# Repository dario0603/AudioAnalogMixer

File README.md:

# Analog Audio Mixer

## Overview

Design and development of a **modular analog audio mixer**, combining circuit simulation and PCB design. The project focuses on audio signal conditioning, equalization, level control, and the integration of multiple input channels into a modular mixer architecture.

The design is divided into two main development areas:

- **LTspice simulations:** individual analog circuit blocks are simulated and evaluated before hardware implementation.
- **KiCad designs:** modular PCB boards are developed to organize the mixer circuitry into functional sections.

The current design includes microphone/line signal conditioning, a three-band equalizer, level and FX-send circuitry, a clipping indicator, and a four-channel mixer board.

The project is still under development. Circuit design, simulation, and PCB integration are ongoing, and the current files should be considered work in progress rather than a finalized hardware design.

## System Architecture

The mixer is organized into modular functional blocks. This approach makes it possible to develop and test each section independently before integrating the complete system.
The input stage provides microphone and line-level signal conditioning. Separate configurations are included for a single microphone/line channel and for two line-level channels, intended for left and right stereo signals.

The signal-conditioning section includes:

- Microphone/line preamplification.
- Three-band tone control.
- Output-level adjustment.
- FX-send circuitry.

### 1. Microphone/Line Preamplifier Circuit

The microphone/line preamplifier circuit provides input signal conditioning and amplification for low-level microphone signals and line-level audio sources. It is designed to adapt different input signal levels to the following stages of the mixer, ensuring proper signal amplification and compatibility with the audio processing circuitry.

### 2. Three-Band Equalizer

The three-band equalizer provides independent control over the low-, mid-, and high-frequency portions of the audio spectrum.

The frequency response is evaluated through LTspice AC analysis. Different equalizer settings are compared to investigate how the circuit affects the audio signal across the frequency range.

### 3. Mixer Unit

This stage combines the signals processed by the input stages (microphone/line preamplifier and three-band equalizer), summing the individual channels to generate the final audio output. The output is provided in differential mode through two dedicated buffer amplifiers, ensuring proper signal driving capability and output impedance.

### 4. Clipping Indicator

A dedicated clipping-indicator circuit is included in the LTspice project.

The circuit uses an LM393 comparator model to detect signal levels approaching the selected clipping threshold. The output can be used to drive an LED, providing a visual indication of excessive signal amplitude.

The comparator circuit is simulated separately to allow its operation and threshold behavior to be evaluated independently of the complete mixer.

## Simulations

### 1. Three-Band Equalizer

**Frequency Response Analysis**

The frequency response of the three-band equalizer is analyzed for different control settings, including low-frequency, mid-frequency, and high-frequency attenuation.

| Low-frequency cut | Mid-frequency cut | High-frequency cut |
|:---:|:---:|:---:|
|  |  |  |

**Flat Frequency Response Analysis**

The overall frequency response is evaluated with all equalizer controls set to their neutral positions.

**Monte Carlo Frequency Response Analysis**

A Monte Carlo analysis is performed to evaluate the effect of component tolerances on the equalizer response, considering 1% resistor tolerances (0603 package) and 10% ceramic X7R capacitor tolerances.

### 2. Microphone/Line Preamplifier

**AC Frequency Response Analysis**

The frequency response of the line and XLR preamplifier configurations is evaluated through LTspice AC analysis to characterize their behavior across the audio frequency range.

**Line Preamplifier:**

**XLR Preamplifier:**

**Transient Response Analysis – 5 kHz Differential Input**

A 5 kHz differential sinusoidal signal is applied to the XLR preamplifier to evaluate its transient response under maximum and minimum gain configurations.

**Input Signal:**

**Maximum Gain Configuration:**

**Minimum Gain Configuration:**

**Monte Carlo Transient Analysis**

A Monte Carlo simulation consisting of 300 runs is performed to evaluate the variability of the XLR preamplifier transient response due to component tolerances, considering both maximum and minimum gain configurations.

**Maximum Gain Configuration:**

**Minimum Gain Configuration:**

**Noise Analysis**

LTspice noise analysis is performed to evaluate the output noise spectral density of the preamplifier stages. Different operational-amplifier configurations are compared to investigate their noise contributions.

The noise simulations are still being refined, particularly regarding the accuracy of the operational-amplifier noise models and their consistency with datasheet specifications.

### 3. Mixer

**Transient Response Analysis**

Transient simulations are performed to evaluate the time-domain behavior of the mixer circuit.

**Monte Carlo Transient Analysis**

A Monte Carlo simulation consisting of 300 runs is performed to investigate output voltage variations caused by component tolerances.

.png)

## PCB Design

The PCB development is carried out in KiCad. The modular approach separates the main mixer board from the input signal-conditioning circuitry.

### 1. Four-Channel Mixer Board

The `4ChannelMixerBoard` project contains the PCB design and schematic for the four-channel mixer board.

The board is intended to provide the central platform for combining the individual audio channels.

### 2. Single-Channel Microphone/Line Board

The `SignalConditioning - OneChannel - Mic-Line` project contains the signal-conditioning design for a single microphone/line input channel.
The PCB layout brings the microphone/line preamplifier, three-band equalizer, level and FX-send circuitry, and power supply together on a single board.

The project includes the following schematic sections:

- Microphone/line preamplifier.
- Three-band equalizer.
- Level control and FX-send circuitry.
- Power supply.

### 3. Two-Channel Line Board

The `SignalConditioning - TwoChannels - R-L-Line` project contains a two-channel signal-conditioning configuration intended for right and left line-level signals.

Its schematic is organized around the same functional blocks as the single-channel version, adapted for a stereo input configuration.

The PCB layouts and circuit integration are still under development. Further work is required to complete the board designs and verify their operation in hardware.

## Repository Structure

```text
.
├── README.md
│
├── AudioMixer - LTSpice/
│   ├── 3bEq/
│   │   ├── AudioMixer - 3bEq.asc
│   │   ├── NE5532.sub
│   │   └── Montecarlo/
│   │
│   ├── ClippingLed/
│   │   ├── ClippingLed.asc
│   │   └── lm393.lib
│   │
│   └── Mic-Line amplifier/
│       ├── AudioMixer - Mic-Line-amp.asc
│       └── NE5532.sub
│
├── AudioMixer - ModularBoards/
│   ├── spec.txt
│   │
│   ├── 4ChannelMixerBoard/
│   │   ├── Mixer_circuit.kicad_pro
│   │   ├── Mixer_circuit.kicad_sch
│   │   └── Mixer_circuit.kicad_pcb
│   │
│   ├── SignalConditioning - OneChannel - Mic-Line/
│   │   ├── AudioMixer.kicad_pro
│   │   ├── AudioMixer.kicad_sch
│   │   ├── AudioMixer.kicad_pcb
│   │   ├── Mic-Line_preamp.kicad_sch
│   │   ├── 3_band_equalizer.kicad_sch
│   │   ├── Level_and_FXSend.kicad_sch
│   │   └── Power_supply.kicad_sch
│   │
│   └── SignalConditioning - TwoChannels - R-L-Line/
│       ├── AudioMixer.kicad_pro
│       ├── AudioMixer.kicad_sch
│       ├── AudioMixer.kicad_pcb
│       ├── Mic-Line_preamp.kicad_sch
│       ├── 3_band_equalizer.kicad_sch
│       ├── Level_and_FXSend.kicad_sch
│       └── Power_supply.kicad_sch
│
└── img/
```

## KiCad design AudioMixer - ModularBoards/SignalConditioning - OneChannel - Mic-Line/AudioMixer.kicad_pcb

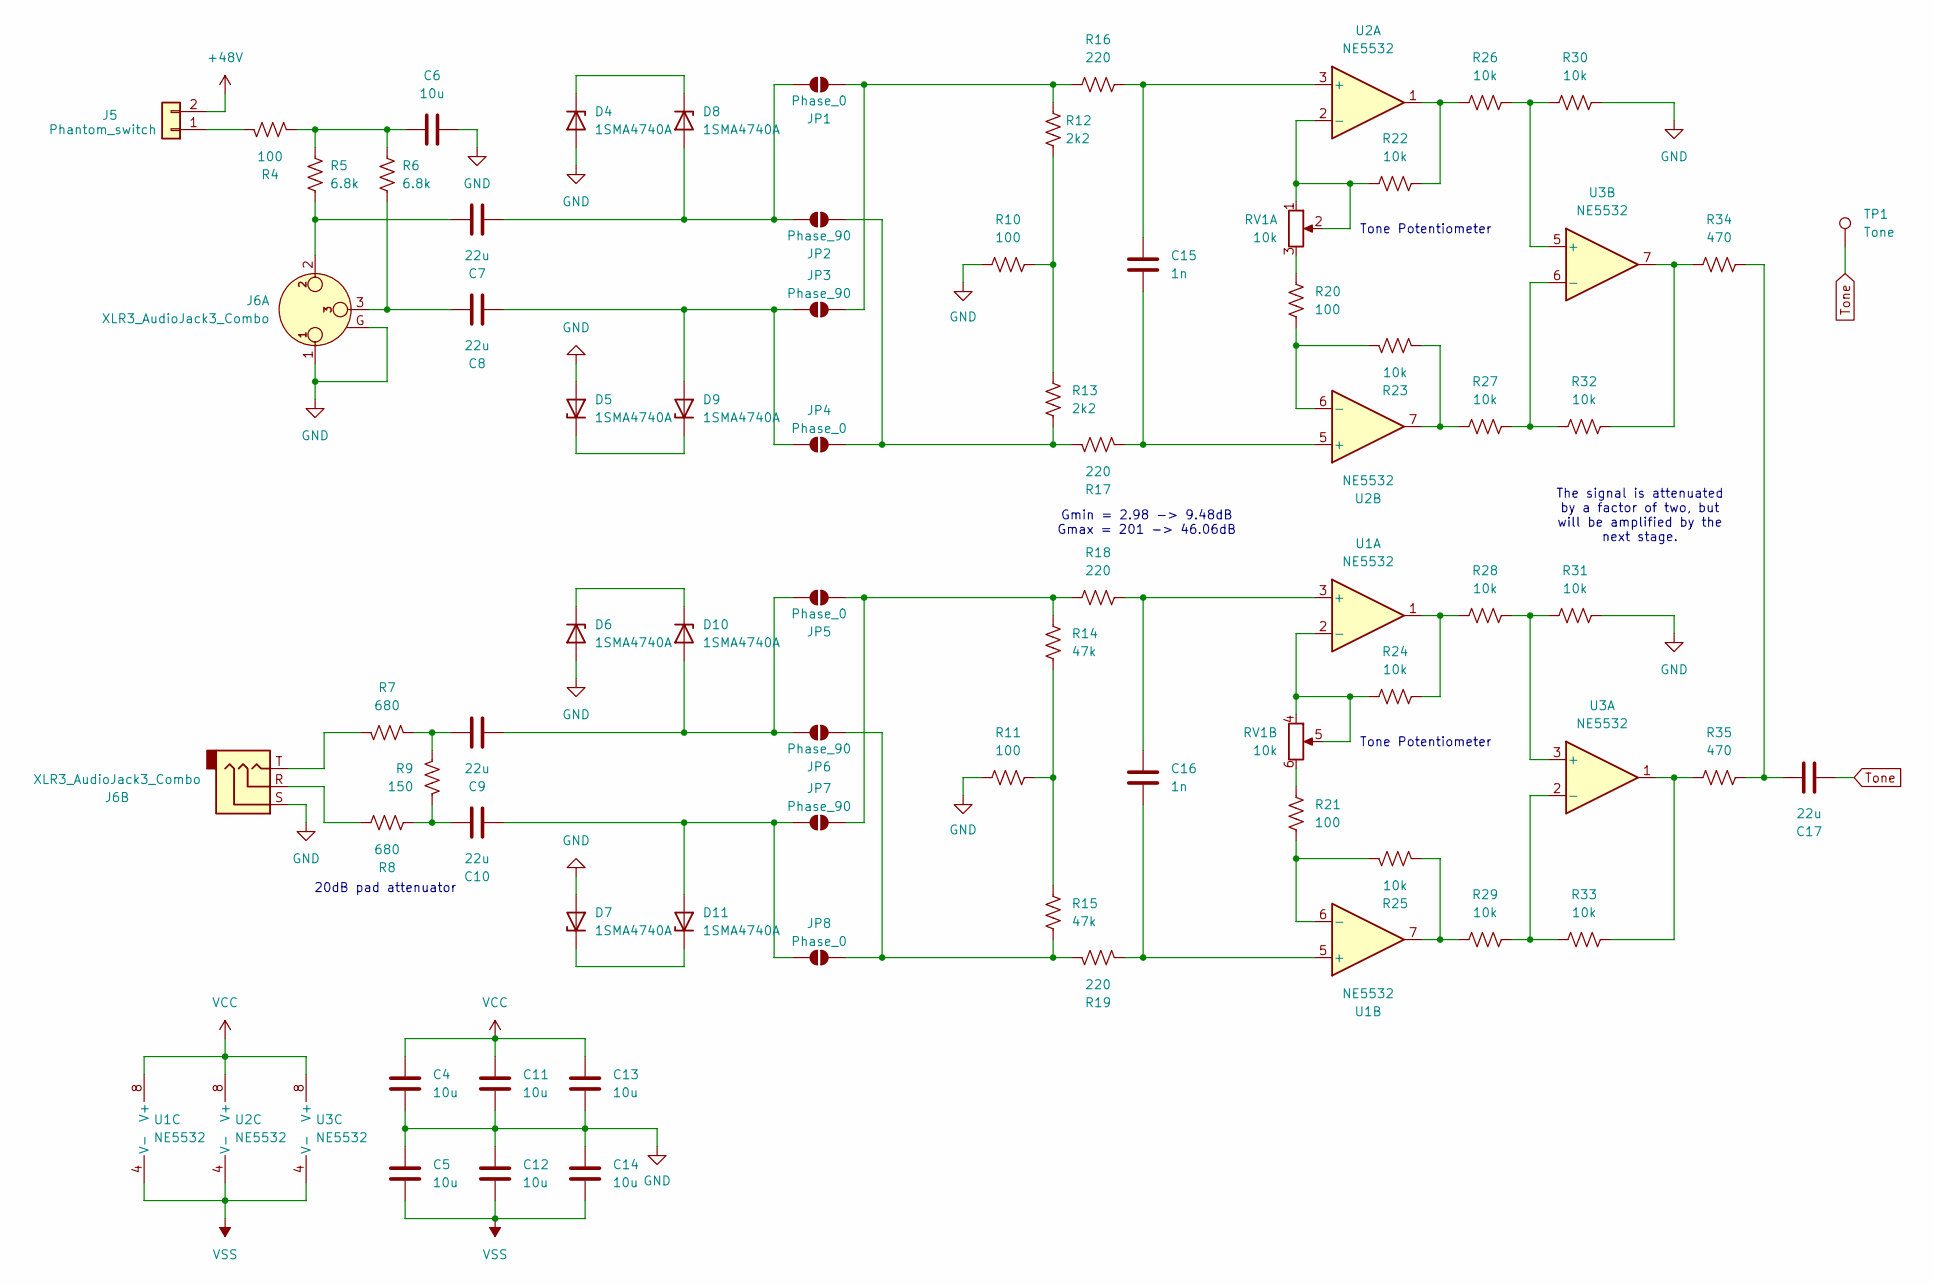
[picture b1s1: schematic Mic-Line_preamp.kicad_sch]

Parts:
C4, C5, C6, C11, C12, C13, C14: 10u; C_0805_2012Metric_Pad1.18x1.45mm_HandSolder
C7, C8, C9, C10, C17: 22u; C_0805_2012Metric_Pad1.18x1.45mm_HandSolder
C15, C16: 1n; C_0603_1608Metric_Pad1.08x0.95mm_HandSolder
D4, D5, D6, D7, D8, D9, D10, D11: 1SMA4740A; D_SMA
J5: Phantom_switch; PinHeader_1x02_P2.54mm_Vertical
J6: XLR3_AudioJack3_Combo; Jack_XLR-6.35mm_Neutrik_NCJ6FI-H_Horizontal
JP1, JP4, JP5, JP8: Phase_0; SolderJumper-2_P1.3mm_Open_RoundedPad1.0x1.5mm
JP2, JP3, JP6, JP7: Phase_90; SolderJumper-2_P1.3mm_Open_RoundedPad1.0x1.5mm
R4: 100; R_1206_3216Metric_Pad1.30x1.75mm_HandSolder
R5, R6: 6.8k; R_1206_3216Metric_Pad1.30x1.75mm_HandSolder
R7, R8: 680; R_0603_1608Metric_Pad0.98x0.95mm_HandSolder
R9: 150; R_0603_1608Metric_Pad0.98x0.95mm_HandSolder
R10, R11, R20, R21: 100; R_0603_1608Metric_Pad0.98x0.95mm_HandSolder
R12, R13: 2k2; R_0603_1608Metric_Pad0.98x0.95mm_HandSolder
R14, R15: 47k; R_0603_1608Metric_Pad0.98x0.95mm_HandSolder
R16, R17, R18, R19: 220; R_0603_1608Metric_Pad0.98x0.95mm_HandSolder
R22, R23, R24, R25, R26, R27, R28, R29, R30, R31, R32, R33: 10k; R_0603_1608Metric_Pad0.98x0.95mm_HandSolder
R34, R35: 470; R_0603_1608Metric_Pad0.98x0.95mm_HandSolder
RV1: 10k; Potentiometer_Alps_RK097_Dual_Horizontal
TP1: Tone; TestPoint_Pad_D1.0mm
U1, U2, U3: NE5532; SOIC-8_3.9x4.9mm_P1.27mm

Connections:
+48V: J5.2; also elsewhere on the board
GND: C4.2, C5.1, C6.1, C11.2, C12.1, C13.2, C14.1, D4.2 (A), D5.2 (A), D6.2 (A), D7.2 (A), J6.1, J6.G, J6.S, R10.1, R11.2, R30.1, R31.1; also elsewhere on the board
unnamed: C6.2, R4.1, R5.2, R6.2
unnamed: C7.1, J6.2, R5.1
unnamed: C8.1, J6.3, R6.1
unnamed: C9.1, R7.2, R9.2
unnamed: C10.1, R8.2, R9.1
unnamed: C17.1, R34.2, R35.2
unnamed: D4.1 (K), D8.1 (K)
unnamed: D5.1 (K), D9.1 (K)
unnamed: C7.2, D8.2 (A), JP1.1 (A), JP2.1 (A)
unnamed: C8.2, D9.2 (A), JP3.1 (A), JP4.1 (A)
unnamed: C9.2, D10.2 (A), JP5.1 (A), JP6.1 (A)
unnamed: D6.1 (K), D10.1 (K)
unnamed: C10.2, D11.2 (A), JP7.1 (A), JP8.1 (A)
unnamed: D7.1 (K), D11.1 (K)
unnamed: J5.1, R4.2
unnamed: J6.R, R8.1
unnamed: J6.T, R7.1
unnamed: JP1.2 (B), JP3.2 (B), R12.1, R16.2
unnamed: JP2.2 (B), JP4.2 (B), R13.2, R17.2
unnamed: JP5.2 (B), JP7.2 (B), R14.1, R18.2
unnamed: JP6.2 (B), JP8.2 (B), R15.2, R19.2
unnamed: R10.2, R12.2, R13.1
unnamed: R11.1, R14.2, R15.1
unnamed: R20.1, RV1.3
unnamed: R21.1, RV1.6
unnamed: R22.1, R26.2, U2.1
unnamed: R23.1, R27.2, U2.7
unnamed: R24.1, R28.2, U1.1
unnamed: R25.1, R29.2, U1.7
unnamed: R32.1, R34.1, U3.7
unnamed: R33.1, R35.1, U3.1
unnamed: C16.1, R18.1, U1.3 (+)
unnamed: R24.2, RV1.4, RV1.5, U1.2 (-)
unnamed: C16.2, R19.1, U1.5 (+)
unnamed: R21.2, R25.2, U1.6 (-)
unnamed: C15.1, R16.1, U2.3 (+)
unnamed: R22.2, RV1.1, RV1.2, U2.2 (-)
unnamed: C15.2, R17.1, U2.5 (+)
unnamed: R20.2, R23.2, U2.6 (-)
unnamed: R28.1, R31.2, U3.3 (+)
unnamed: R29.1, R33.2, U3.2 (-)
unnamed: R26.1, R30.2, U3.5 (+)
unnamed: R27.1, R32.2, U3.6 (-)
Tone: C17.2, TP1.1; also elsewhere on the board
VCC: C4.1, C11.1, C13.1, U1.8 (V+), U2.8 (V+), U3.8 (V+); also elsewhere on the board
VSS: C5.2, C12.2, C14.2, U1.4 (V-), U2.4 (V-), U3.4 (V-); also elsewhere on the board

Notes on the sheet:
Gmin = 2.98 -> 9.48dB Gmax = 201 -> 46.06dB
Tone Potentiometer
20dB pad attenuator
The signal is attenuated by a factor of two, but will be amplified by the next stage.

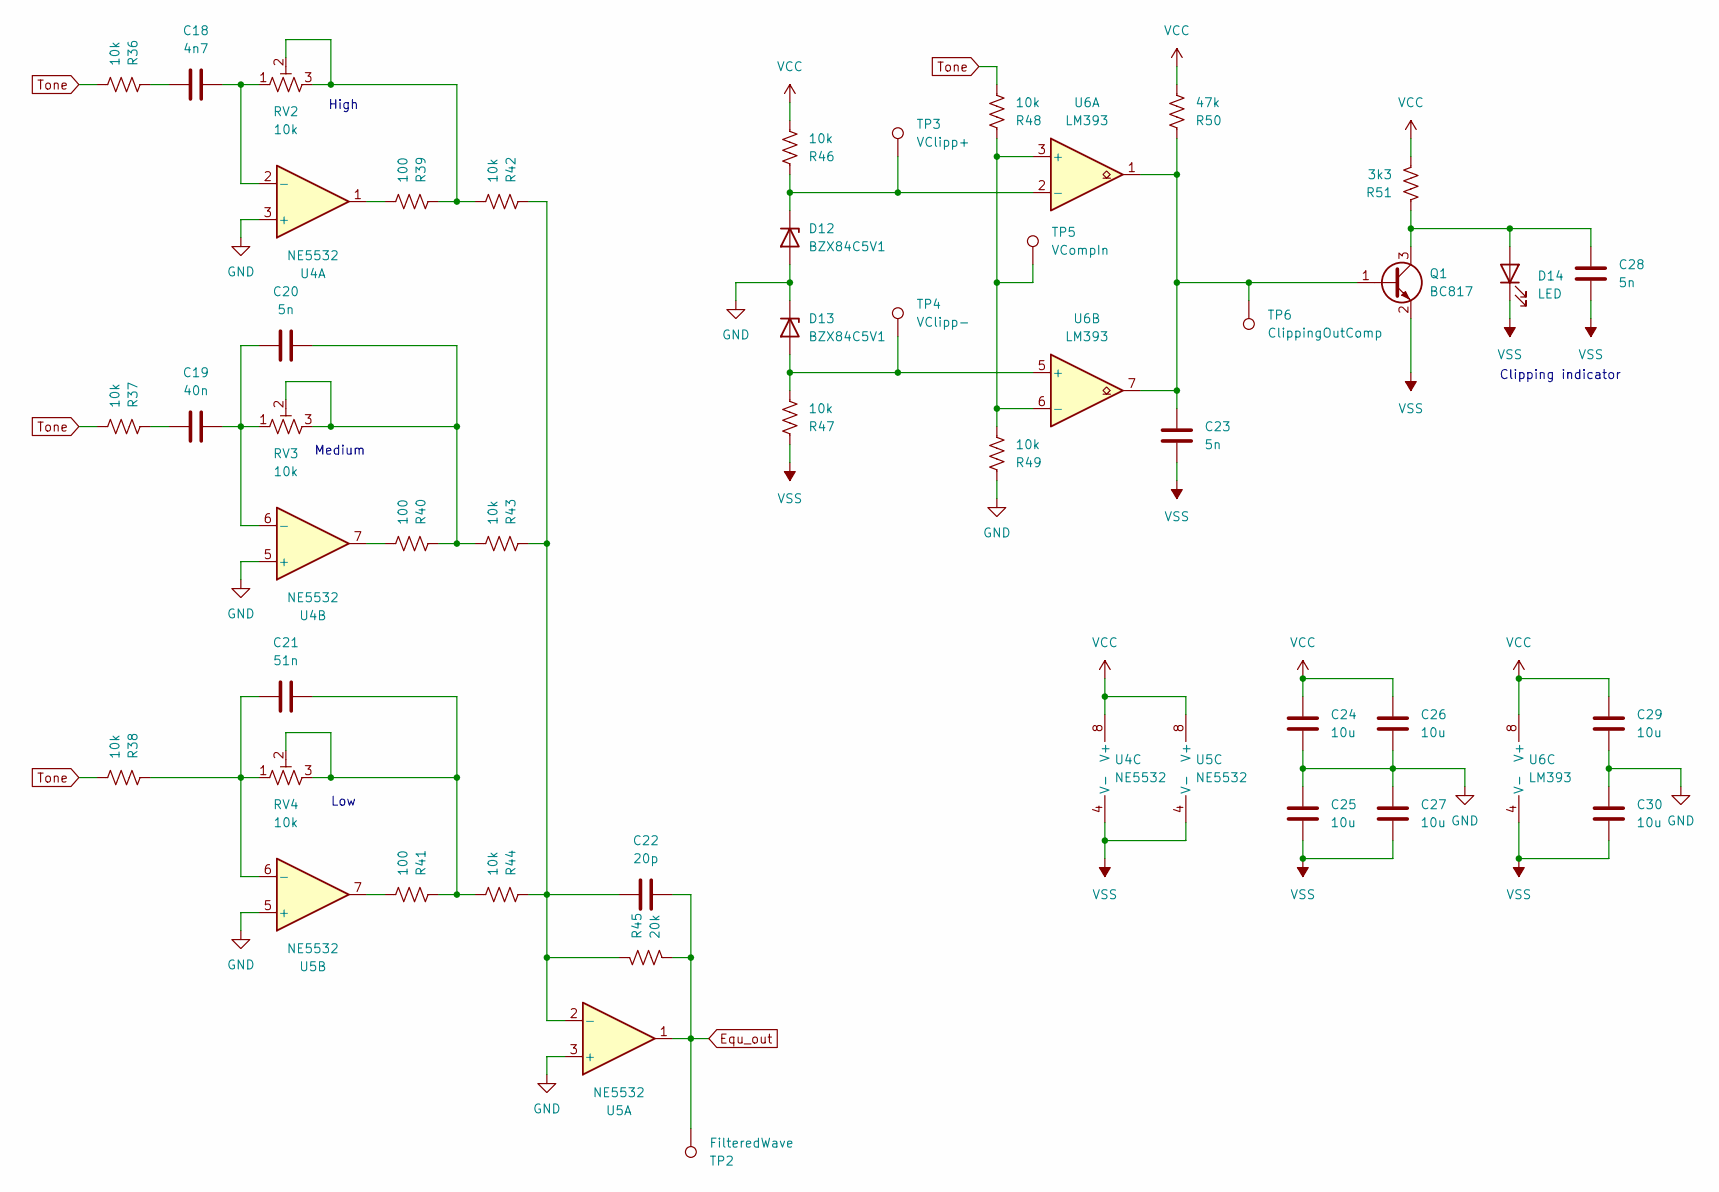
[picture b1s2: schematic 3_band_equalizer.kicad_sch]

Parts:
C18: 4n7; C_0603_1608Metric_Pad1.08x0.95mm_HandSolder
C19: 40n; C_0603_1608Metric_Pad1.08x0.95mm_HandSolder
C20, C23, C28: 5n; C_0603_1608Metric_Pad1.08x0.95mm_HandSolder
C21: 51n; C_0603_1608Metric_Pad1.08x0.95mm_HandSolder
C22: 20p; C_0603_1608Metric_Pad1.08x0.95mm_HandSolder
C24, C25, C26, C27, C29, C30: 10u; C_0805_2012Metric_Pad1.18x1.45mm_HandSolder
D12, D13: BZX84C5V1; SOT-23
D14: LED; LED_D3.0mm
Q1: BC817; SOT-23
R36, R37, R38, R42, R43, R44, R46, R47, R48, R49: 10k; R_0603_1608Metric_Pad0.98x0.95mm_HandSolder
R39, R40, R41: 100; R_0603_1608Metric_Pad0.98x0.95mm_HandSolder
R45: 20k; R_0603_1608Metric_Pad0.98x0.95mm_HandSolder
R50: 47k; R_0603_1608Metric_Pad0.98x0.95mm_HandSolder
R51: 3k3; R_0603_1608Metric_Pad0.98x0.95mm_HandSolder
RV2, RV3, RV4: 10k; Potentiometer_Alps_RK097_Single_Horizontal
TP2: FilteredWave; TestPoint_Pad_D1.0mm
TP3: VClipp+; TestPoint_Pad_D1.0mm
TP4: VClipp-; TestPoint_Pad_D1.0mm
TP5: VCompIn; TestPoint_Pad_D1.0mm
TP6: ClippingOutComp; TestPoint_Pad_D1.0mm
U4, U5: NE5532; SOIC-8_3.9x4.9mm_P1.27mm
U6: LM393; SOIC-8_3.9x4.9mm_P1.27mm

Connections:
Equ_out: C22.2, R45.2, TP2.1, U5.1; also elsewhere on the board
GND: C24.2, C25.1, C26.2, C27.1, C29.2, C30.1, D12.1 (A), D13.3 (K), R49.1, U4.3 (+), U4.5 (+), U5.3 (+), U5.5 (+); also elsewhere on the board
unnamed: C18.2, R36.1
unnamed: C19.2, R37.1
unnamed: C20.1, R40.1, R43.2, RV3.2, RV3.3
unnamed: C21.1, R41.1, R44.2, RV4.2, RV4.3
unnamed: D12.3 (K), R46.1, TP3.1, U6.2 (-)
unnamed: D13.1 (A), R47.2, TP4.1, U6.5 (+)
unnamed: C28.1, D14.2 (A), Q1.3 (C), R51.1
unnamed: C23.1, Q1.1 (B), R50.1, TP6.1, U6.1, U6.7
unnamed: R39.1, R42.2, RV2.2, RV2.3
unnamed: R39.2, U4.1
unnamed: R40.2, U4.7
unnamed: R41.2, U5.7
unnamed: C18.1, RV2.1, U4.2 (-)
unnamed: C19.1, C20.2, RV3.1, U4.6 (-)
unnamed: C22.1, R42.1, R43.1, R44.1, R45.1, U5.2 (-)
unnamed: C21.2, R38.1, RV4.1, U5.6 (-)
unnamed: R48.1, R49.2, TP5.1, U6.3 (+), U6.6 (-)
Tone: R36.2, R37.2, R38.2, R48.2; also elsewhere on the board
VCC: C24.1, C26.1, C29.1, R46.2, R50.2, R51.2, U4.8 (V+), U5.8 (V+), U6.8 (V+); also elsewhere on the board
VSS: C23.2, C25.2, C27.2, C28.2, C30.2, D14.1 (K), Q1.2 (E), R47.1, U4.4 (V-), U5.4 (V-), U6.4 (V-); also elsewhere on the board

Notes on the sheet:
High
Medium
Clipping indicator
Low

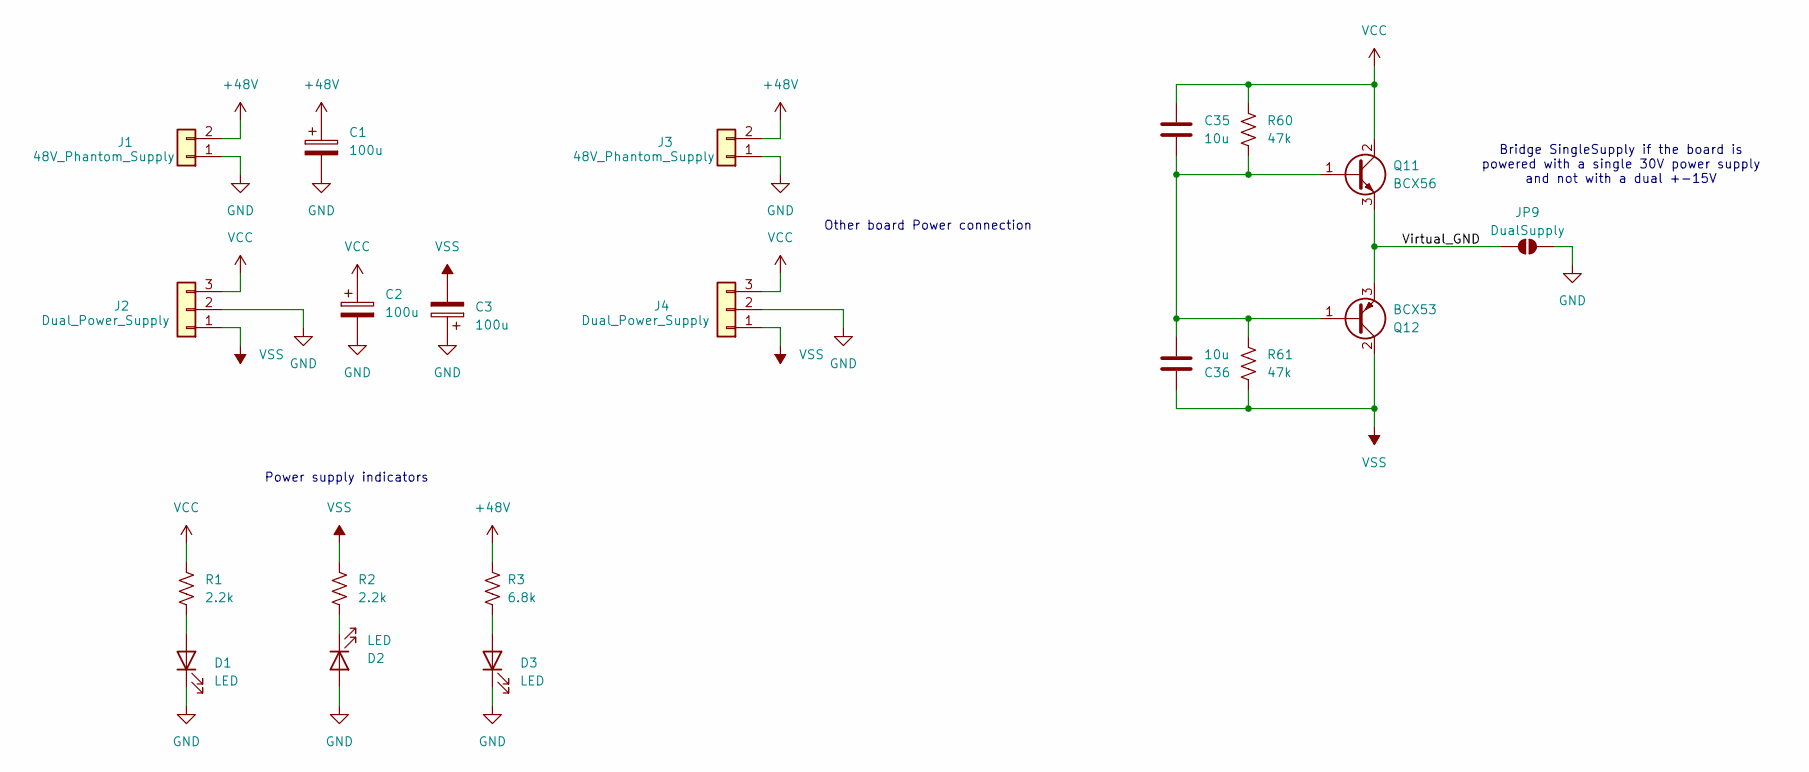
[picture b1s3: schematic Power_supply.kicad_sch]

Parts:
C1, C2, C3: 100u; CP_Radial_D8.0mm_P3.50mm
C35, C36: 10u; C_0805_2012Metric_Pad1.18x1.45mm_HandSolder
D1, D2, D3: LED; LED_D3.0mm
J1, J3: 48V_Phantom_Supply; PinHeader_1x02_P2.54mm_Vertical
J2, J4: Dual_Power_Supply; PinHeader_1x03_P2.54mm_Vertical
JP9: DualSupply; SolderJumper-2_P1.3mm_Open_RoundedPad1.0x1.5mm
Q11: BCX56; SOT-89-3
Q12: BCX53; SOT-89-3
R1, R2: 2.2k; R_1206_3216Metric_Pad1.30x1.75mm_HandSolder
R3: 6.8k; R_1206_3216Metric_Pad1.30x1.75mm_HandSolder
R60, R61: 47k; R_0603_1608Metric_Pad0.98x0.95mm_HandSolder

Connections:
+48V: C1.1, J1.2, J3.2, R3.2; also elsewhere on the board
/Power supply/Virtual_GND: JP9.1 (A), Q11.3 (E), Q12.3 (E)
GND: C1.2, C2.2, C3.1, D1.1 (K), D2.2 (A), D3.1 (K), J1.1, J2.2, J3.1, J4.2, JP9.2 (B); also elsewhere on the board
unnamed: D1.2 (A), R1.1
unnamed: D2.1 (K), R2.1
unnamed: D3.2 (A), R3.1
unnamed: C35.2, C36.2, Q11.1 (B), Q12.1 (B), R60.2, R61.1
VCC: C2.1, C35.1, J2.3, J4.3, Q11.2 (C), R1.2, R60.1; also elsewhere on the board
VSS: C3.2, C36.1, J2.1, J4.1, Q12.2 (C), R2.2, R61.2; also elsewhere on the board

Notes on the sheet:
Bridge SingleSupply if the board is powered with a single 30V power supply and not with a dual +-15V
Other board Power connection
Power supply indicators

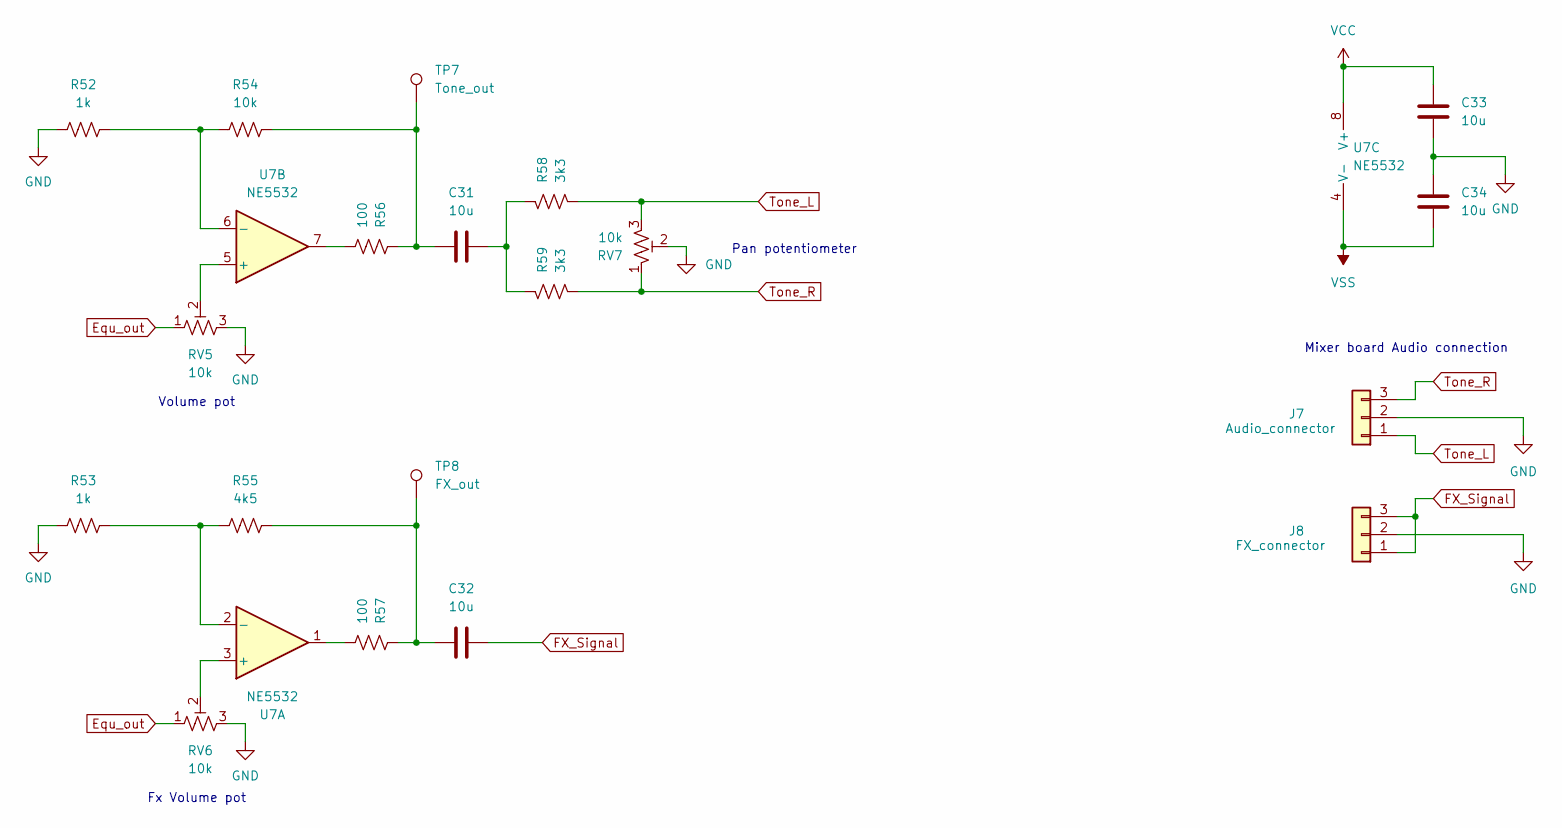
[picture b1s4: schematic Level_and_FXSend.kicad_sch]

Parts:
C31, C32, C33, C34: 10u; C_0805_2012Metric_Pad1.18x1.45mm_HandSolder
J7: Audio_connector; PinHeader_1x03_P2.54mm_Vertical
J8: FX_connector; PinHeader_1x03_P2.54mm_Vertical
R52, R53: 1k; R_0603_1608Metric_Pad0.98x0.95mm_HandSolder
R54: 10k; R_0603_1608Metric_Pad0.98x0.95mm_HandSolder
R55: 4k5; R_0603_1608Metric_Pad0.98x0.95mm_HandSolder
R56, R57: 100; R_0603_1608Metric_Pad0.98x0.95mm_HandSolder
R58, R59: 3k3; R_0603_1608Metric_Pad0.98x0.95mm_HandSolder
RV5, RV6, RV7: 10k; Potentiometer_Alps_RK097_Single_Horizontal
TP7: Tone_out; TestPoint_Pad_D1.0mm
TP8: FX_out; TestPoint_Pad_D1.0mm
U7: NE5532; SOIC-8_3.9x4.9mm_P1.27mm

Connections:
Equ_out: RV5.1, RV6.1; also elsewhere on the board
FX_Signal: C32.2, J8.1, J8.3
GND: C33.2, C34.1, J7.2, J8.2, R52.2, R53.2, RV5.3, RV6.3, RV7.2; also elsewhere on the board
unnamed: C31.1, R54.1, R56.1, TP7.1
unnamed: C31.2, R58.1, R59.1
unnamed: C32.1, R55.1, R57.1, TP8.1
unnamed: R56.2, U7.7
unnamed: R57.2, U7.1
unnamed: RV6.2, U7.3 (+)
unnamed: R53.1, R55.2, U7.2 (-)
unnamed: RV5.2, U7.5 (+)
unnamed: R52.1, R54.2, U7.6 (-)
Tone_L: J7.1, R58.2, RV7.3
Tone_R: J7.3, R59.2, RV7.1
VCC: C33.1, U7.8 (V+); also elsewhere on the board
VSS: C34.2, U7.4 (V-); also elsewhere on the board

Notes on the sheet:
Mixer board Audio connection
Volume pot
Pan potentiometer
Fx Volume pot

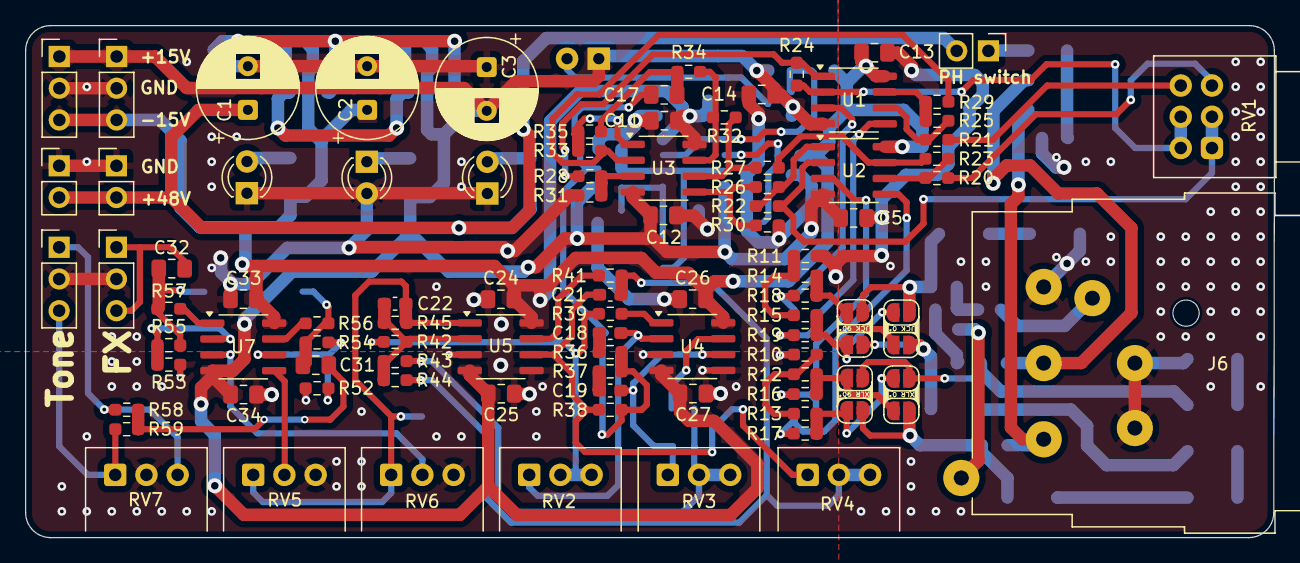
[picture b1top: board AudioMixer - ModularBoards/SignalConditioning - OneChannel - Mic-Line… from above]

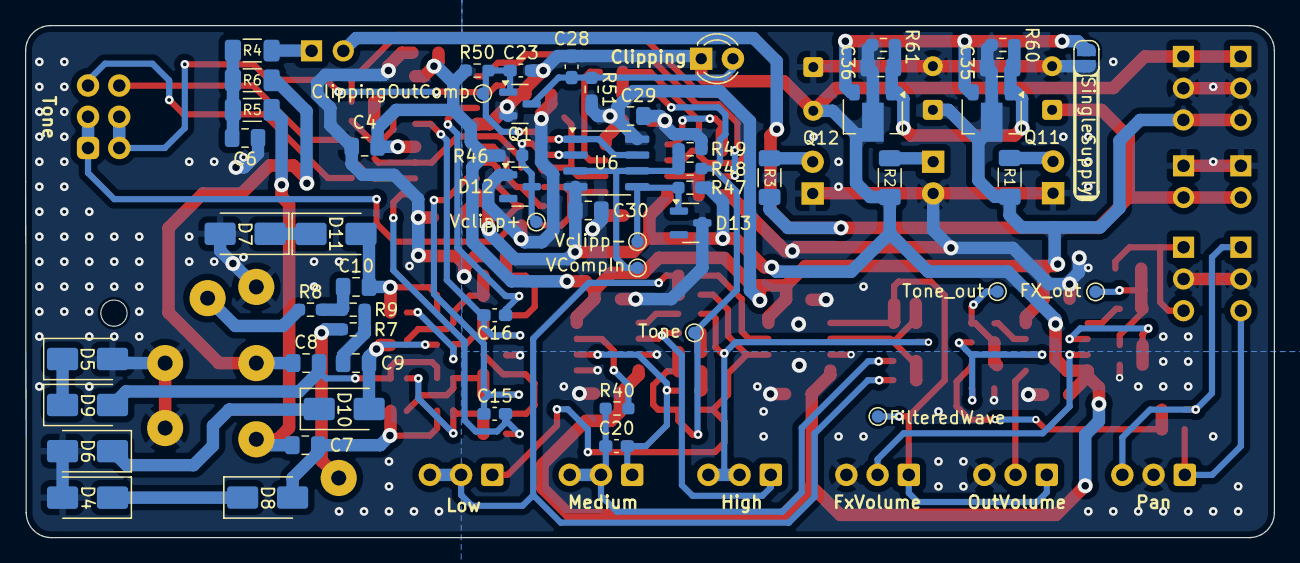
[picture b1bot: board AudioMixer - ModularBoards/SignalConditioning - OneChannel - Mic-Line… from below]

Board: 2 copper layers, 100.0 x 41.0 mm, 153 parts (57 on the bottom side), 83 nets.

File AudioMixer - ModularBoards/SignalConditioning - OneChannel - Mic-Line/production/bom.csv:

Designator,Footprint,Quantity,Value,LCSC Part #
"C1, C2, C3",CP_Radial_D8.0mm_P3.50mm,3,100u,
"C10, C17, C7, C8, C9",0805,5,22u,
"C11, C12, C13, C14, C24, C25, C26, C27, C29, C30, C31, C32, C33, C34, C35, C36, C4, C5, C6",0805,19,10u,
"C15, C16",0603,2,1n,
C18,0603,1,4n7,
C19,0603,1,40n,
"C20, C23, C28",0603,3,5n,
C21,0603,1,51n,
C22,0603,1,20p,
"D1, D14, D2, D3",LED_D3.0mm,4,LED,
"D10, D11, D4, D5, D6, D7, D8, D9",D_SMA,8,1SMA4740A,
"D12, D13",SOT-23,2,BZX84C5V1,
"J1, J3",PinHeader_1x02_P2.54mm_Vertical,2,48V_Phantom_Supply,
"J2, J4",PinHeader_1x03_P2.54mm_Vertical,2,Dual_Power_Supply,
J5,PinHeader_1x02_P2.54mm_Vertical,1,Phantom_switch,
J6,Jack_XLR-6.35mm_Neutrik_NCJ6FI-H_Horizontal,1,XLR3_AudioJack3_Combo,
J7,PinHeader_1x03_P2.54mm_Vertical,1,Audio_connector,
J8,PinHeader_1x03_P2.54mm_Vertical,1,FX_connector,
Q1,SOT-23,1,BC817,
Q11,SOT-89-3,1,BCX56,
Q12,SOT-89-3,1,BCX53,
"R1, R2",1206,2,2.2k,
"R10, R11, R20, R21, R39, R40, R41, R56, R57",0603,9,100,
"R12, R13",0603,2,2k2,
"R14, R15, R50, R60, R61",0603,5,47k,
"R16, R17, R18, R19",0603,4,220,
"R22, R23, R24, R25, R26, R27, R28, R29, R30, R31, R32, R33, R36, R37, R38, R42, R43, R44, R46, R47, R48, R49, R54",0603,23,10k,
"R3, R5, R6",1206,3,6.8k,
"R34, R35",0603,2,470,
R4,1206,1,100,
R45,0603,1,20k,
"R51, R58, R59",0603,3,3k3,
"R52, R53",0603,2,1k,
R55,0603,1,4k5,
"R7, R8",0603,2,680,
R9,0603,1,150,
RV1,Potentiometer_Alps_RK097_Dual_Horizontal,1,10k,
"RV2, RV3, RV4, RV5, RV6, RV7",Potentiometer_Alps_RK097_Single_Horizontal,6,10k,
TP1,TestPoint_Pad_D1.0mm,1,Tone,
TP2,TestPoint_Pad_D1.0mm,1,FilteredWave,
TP3,TestPoint_Pad_D1.0mm,1,VClipp+,
TP4,TestPoint_Pad_D1.0mm,1,VClipp-,
TP5,TestPoint_Pad_D1.0mm,1,VCompIn,
TP6,TestPoint_Pad_D1.0mm,1,ClippingOutComp,
TP7,TestPoint_Pad_D1.0mm,1,Tone_out,
TP8,TestPoint_Pad_D1.0mm,1,FX_out,
"U1, U2, U3, U4, U5, U7",SOIC-8_3.9x4.9mm_P1.27mm,6,NE5532,
U6,SOIC-8_3.9x4.9mm_P1.27mm,1,LM393,
